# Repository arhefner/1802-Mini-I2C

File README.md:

# 1802-Mini-I2C
I2C interface board for the 1802-Mini-PIO

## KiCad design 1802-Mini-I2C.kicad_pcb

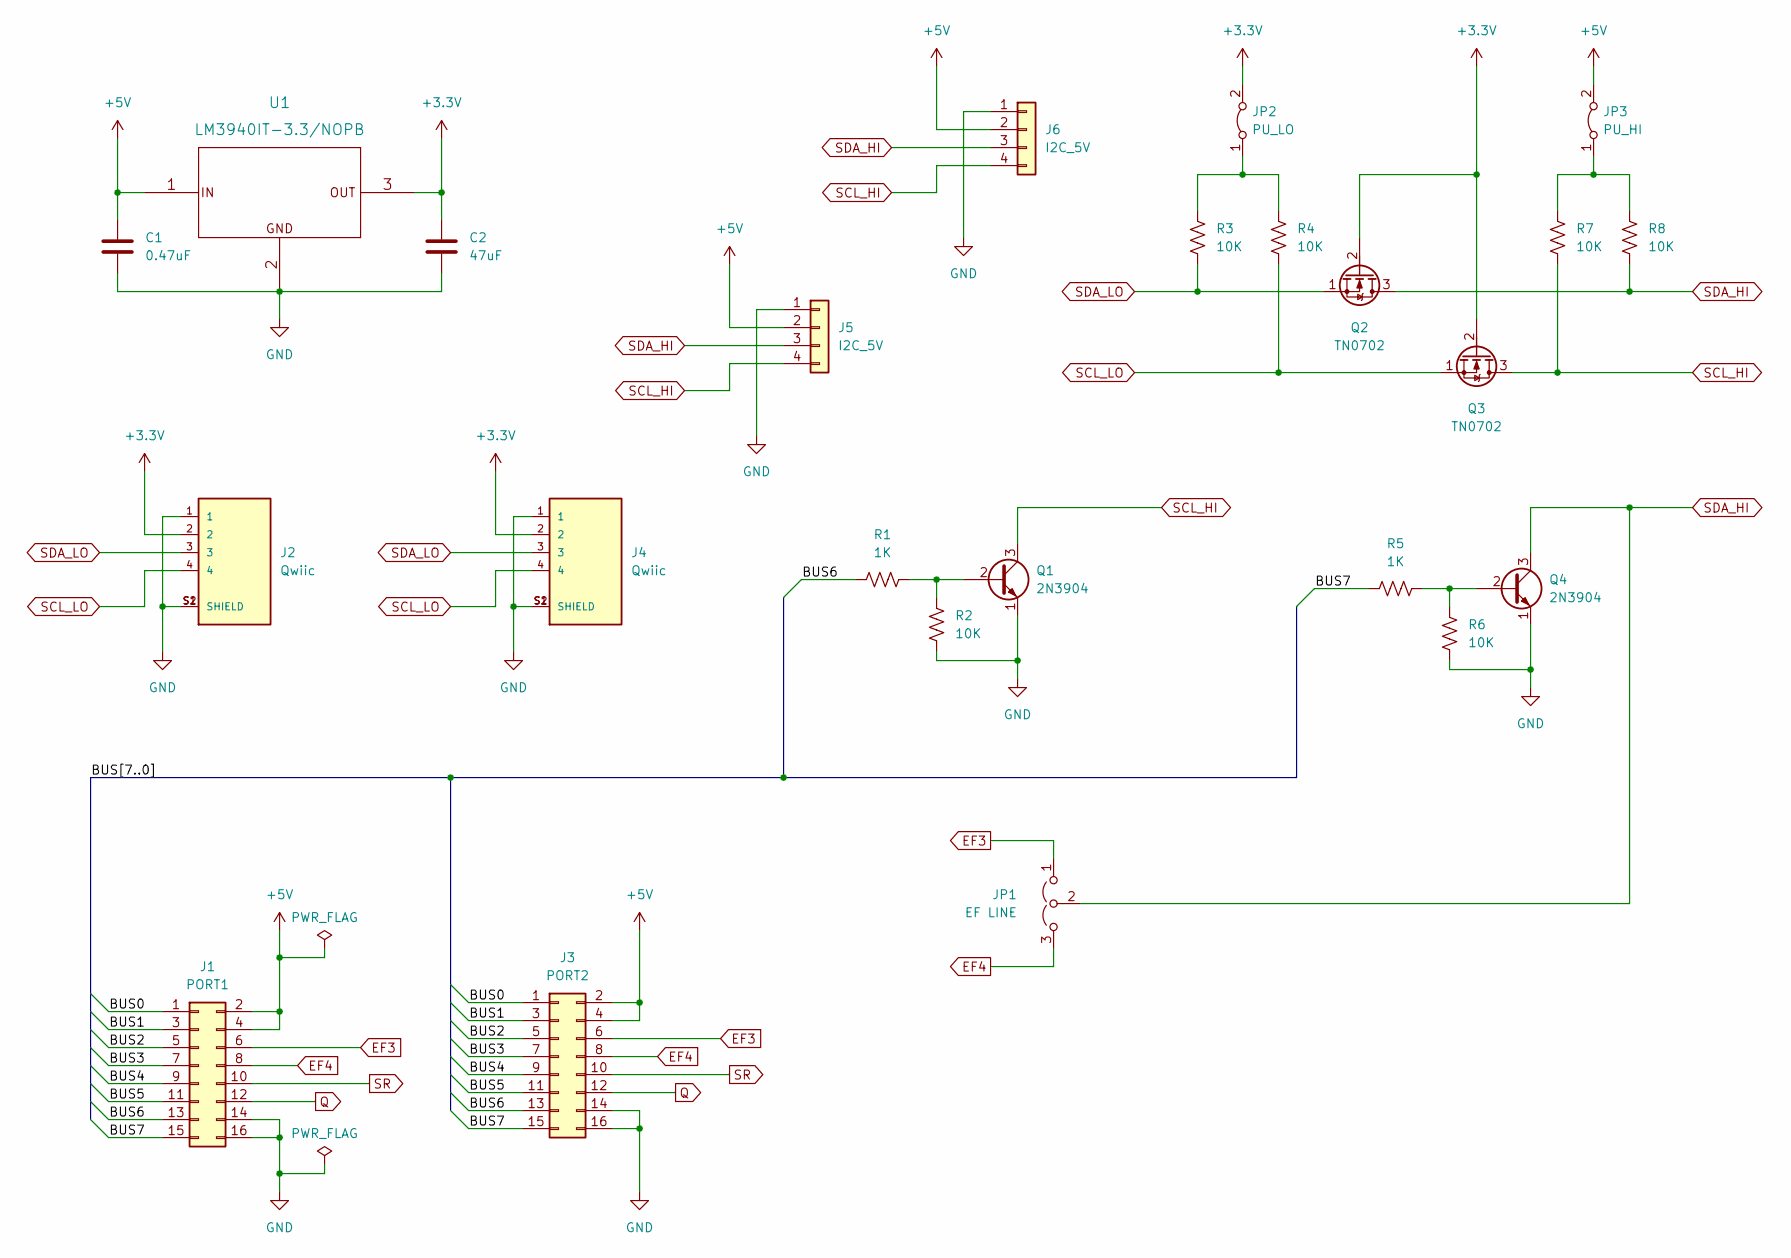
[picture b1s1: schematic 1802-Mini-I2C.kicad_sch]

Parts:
C1: 0.47uF; C_Disc_D5.0mm_W2.5mm_P2.50mm
C2: 47uF; C_Radial_D6.3mm_H11.0mm_P2.50mm
J1: PORT1; PinHeader_2x08_P2.54mm_Vertical
J2, J4: Qwiic; JST_SM04B-SRSS-TB(LF)(SN)
J3: PORT2; PinHeader_2x08_P2.54mm_Vertical
J5, J6: I2C_5V; PinHeader_1x04_P2.54mm_Vertical
JP1: EF LINE; PinHeader_1x03_P2.54mm_Vertical
JP2: PU_LO; PinHeader_1x02_P2.54mm_Vertical
JP3: PU_HI; PinHeader_1x02_P2.54mm_Vertical
Q1, Q4: 2N3904; TO-92
Q2, Q3: TN0702; TO-92
R1, R5: 1K; R_Axial_DIN0207_L6.3mm_D2.5mm_P10.16mm_Horizontal
R2, R3, R4, R6, R7, R8: 10K; R_Axial_DIN0207_L6.3mm_D2.5mm_P10.16mm_Horizontal
U1: LM3940IT-3.3/NOPB; TO-220-3_Horizontal_TabDown

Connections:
+3.3V: C2.1, J2.2, J4.2, JP2.2 (B), Q2.2 (G), Q3.2 (G), U1.3 (OUT)
+5V: C1.1, J1.2, J1.4, J3.2, J3.4, J5.2, J6.2, JP3.2 (B), U1.1 (IN)
/BUS0: J1.1, J3.1
/BUS1: J1.3, J3.3
/BUS2: J1.5, J3.5
/BUS3: J1.7, J3.7
/BUS4: J1.9, J3.9
/BUS5: J1.11, J3.11
/BUS6: J1.13, J3.13, R1.1
/BUS7: J1.15, J3.15, R5.1
EF3: J1.6, J3.6, JP1.1 (A)
EF4: J1.8, J3.8, JP1.3 (B)
GND: C1.2, C2.2, J1.14, J1.16, J2.1, J2.S1 (SHIELD), J2.S2 (SHIELD), J3.14, J3.16, J4.1, J4.S1 (SHIELD), J4.S2 (SHIELD), J5.1, J6.1, Q1.1 (E), Q4.1 (E), R2.1, R6.1, U1.2 (GND)
unnamed: JP2.1 (A), R3.2, R4.2
unnamed: JP3.1 (A), R7.2, R8.2
unnamed: Q1.2 (B), R1.2, R2.2
unnamed: Q4.2 (B), R5.2, R6.2
Q: J1.12, J3.12
SCL_HI: J5.4, J6.4, Q1.3 (C), Q3.3 (D), R7.1
SCL_LO: J2.4, J4.4, Q3.1 (S), R4.1
SDA_HI: J5.3, J6.3, JP1.2 (C), Q2.3 (D), Q4.3 (C), R8.1
SDA_LO: J2.3, J4.3, Q2.1 (S), R3.1
SR: J1.10, J3.10

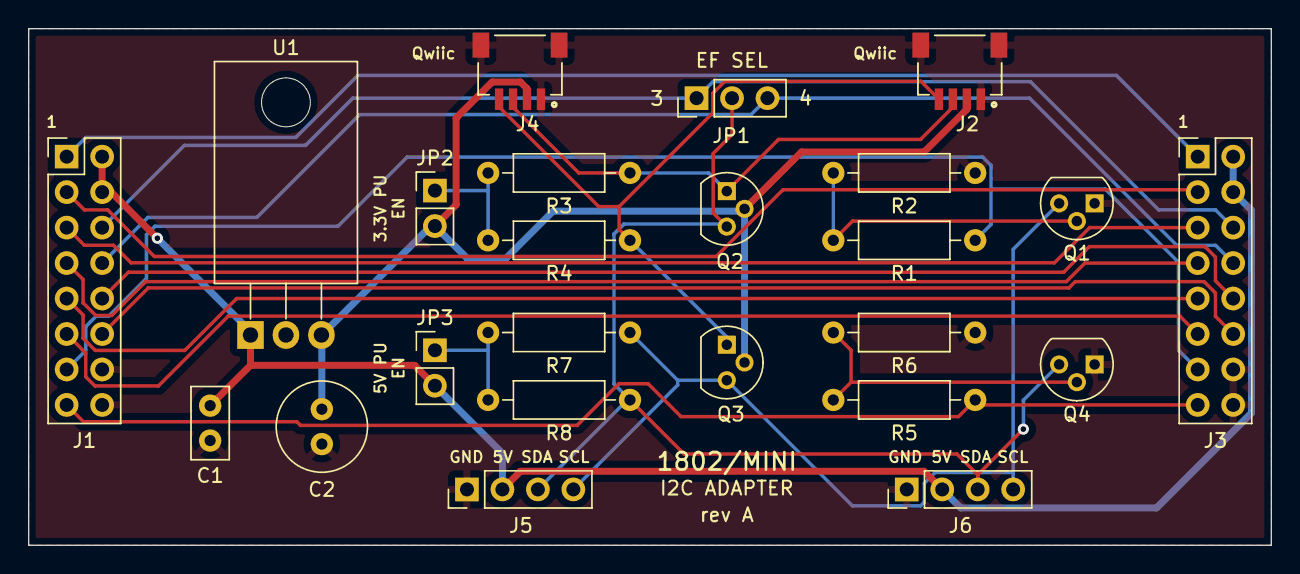
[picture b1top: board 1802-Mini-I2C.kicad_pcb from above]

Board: 2 copper layers, 89.0 x 37.0 mm, 24 parts (0 on the bottom side), 23 nets.

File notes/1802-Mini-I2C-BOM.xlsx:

Please refer to these notes as applicable for the parts list below:
*A | These connectors may be pre-installed on the board.
PARALLEL INTERFACE
Qty | Description |  | Manufacturer | Manufacturer # | Vendor | Vendor # | Price | Qty | Total
Integrated Circuits
1 | LM3940IT-3.3 Regulator | U1 | TI | LM3940IT-3.3/NOPB | Digikey | LM3940IT-3.3/NOPB-ND | 2 | 1 | 2
Discrete Components
2 | Transistor 2N3904 | Q1,Q4 | ON Semi | 2N3904BU | Digikey | 2N3904FS-ND | 0.38 | 2 | 0.76
2 | N Channel FET TN0702 | Q2,Q3 | Microchip | TN0702N3-G | Digikey | TN0702N3-G-ND | 1.44 | 2 | 2.88
1 | Ceramic capacitor 0.47uF radial 2.50mm | C1 | TDK | FG14X7R1E474KNT06 | Digikey | 445-180818-1-ND | 0.35 | 1 | 0.35
1 | Aluminum capacitor 47uF radial 2.50mm | C2 | Kemet | ESY476M050AE3AA | Digikey | 399-ESY476M050AE3AA-ND | 0.33 | 1 | 0.33
2 | Resistor 1/4 watt 1K | R1,R5 | Stackpole | CF14JT1K00 | Digikey | CF14JT1K00CT-ND | 0.1 | 2 | 0.2
6 | Resistor 1/4 watt 10K | R2-R4,R6-R8 | Stackpole | CF14JT10K0 | Digikey | CF14JT10K0CT-ND | 0.1 | 6 | 0.60000000000000009
Interconnects
1 | Straight header 3 pins 0.1" | JP1 | Sullins | PREC003SAAN-RC | Digikey | S1012EC-03-ND | 0.09 | 1 | 0.09
2 | Straight header 2 pins 0.1" | JP2,JP3 | Sullins | PREC002SAAN-RC | Digikey | S1012EC-02-ND | 0.06 | 2 | 0.12
2 | Straight dual row header 8 position | J1,J3 | Sullins | PREC008DAAN-RC | Digikey | S2012EC-08-ND | 0.35 | 2 | 0.7
3 | Jumper shunts 0.1" |  | Sullins | STC02SYAN | Digikey | S9000-ND | 0.09 | 3 | 0.27
2 | R/A header 4 pin 0.1" | J5,J6 | Sullins | PREC004SBAN-M71RC | Digikey | S1112EC-04-ND | 0.15 | 2 | 0.3
2 | R/A 4 pin 1mm pitch connector (Qwiic)(*A) | J2,J4 | JST | SM04B-SRSS-TB(LF)(SN) | Digikey | 455-1804-1-ND | 0.59 | 2 | 1.18
Mechanical
1 | Circuit Board |  | Hefner |  | JLCPCB |  | 5 | 1 | 5
 |  |  |  |  |  |  | Total |  | 14.78

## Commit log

2023-01-14 Update design and add BOM
